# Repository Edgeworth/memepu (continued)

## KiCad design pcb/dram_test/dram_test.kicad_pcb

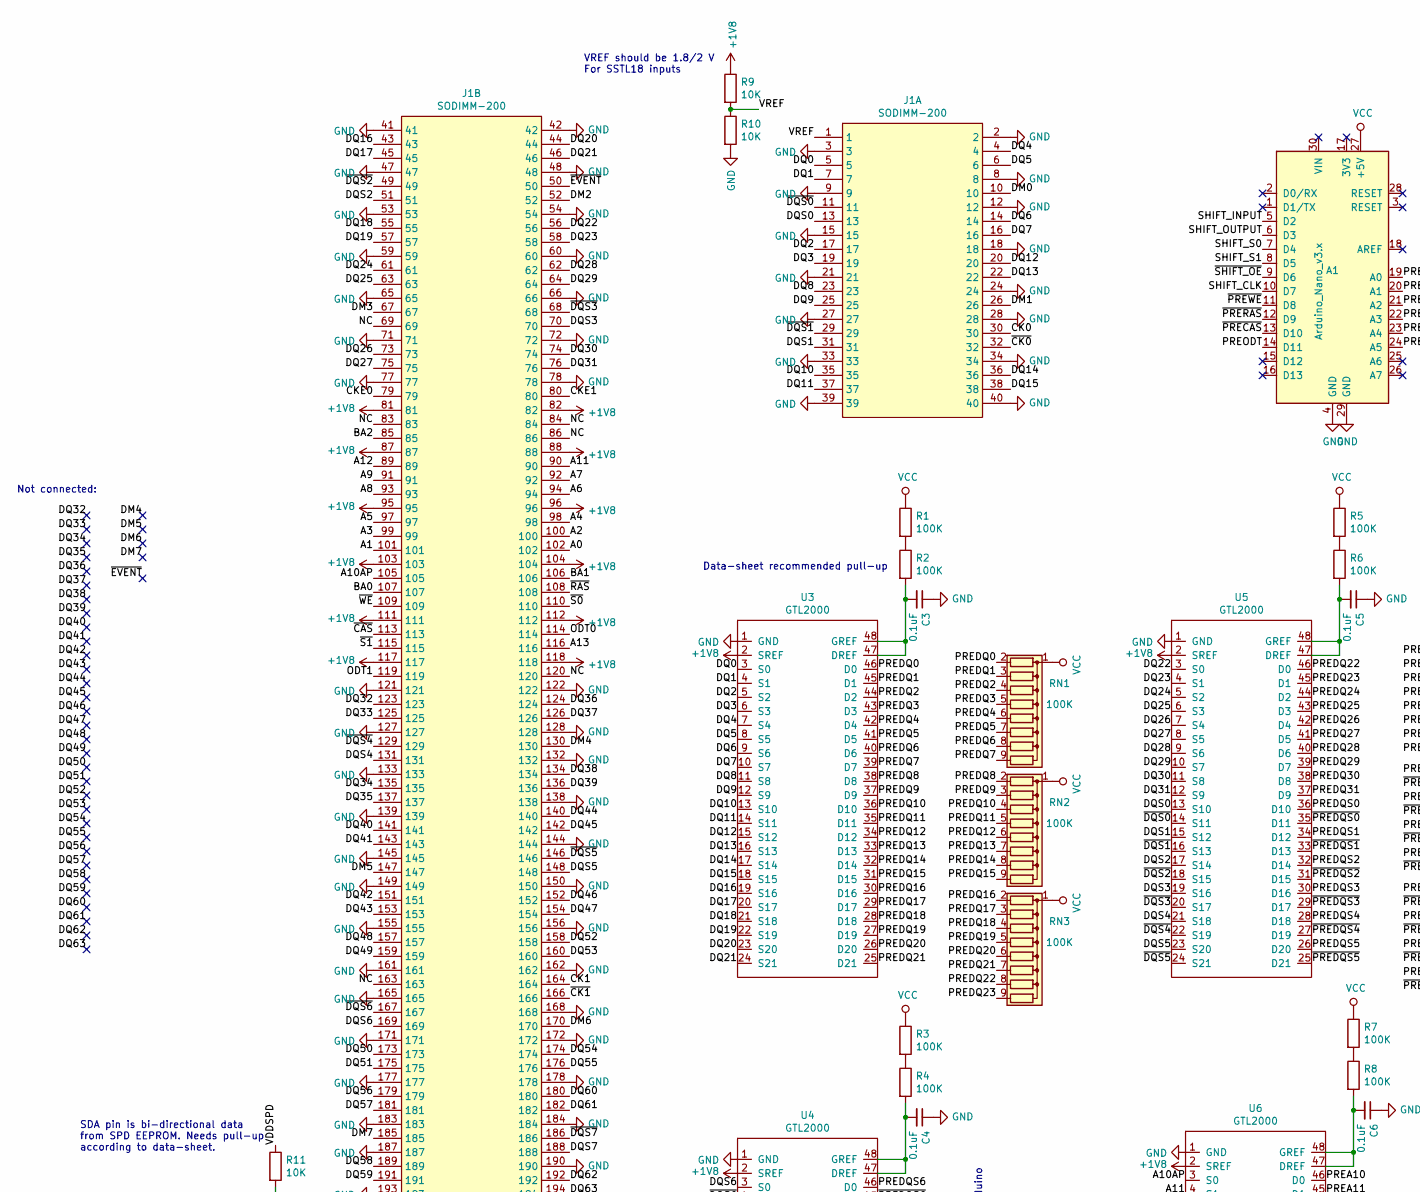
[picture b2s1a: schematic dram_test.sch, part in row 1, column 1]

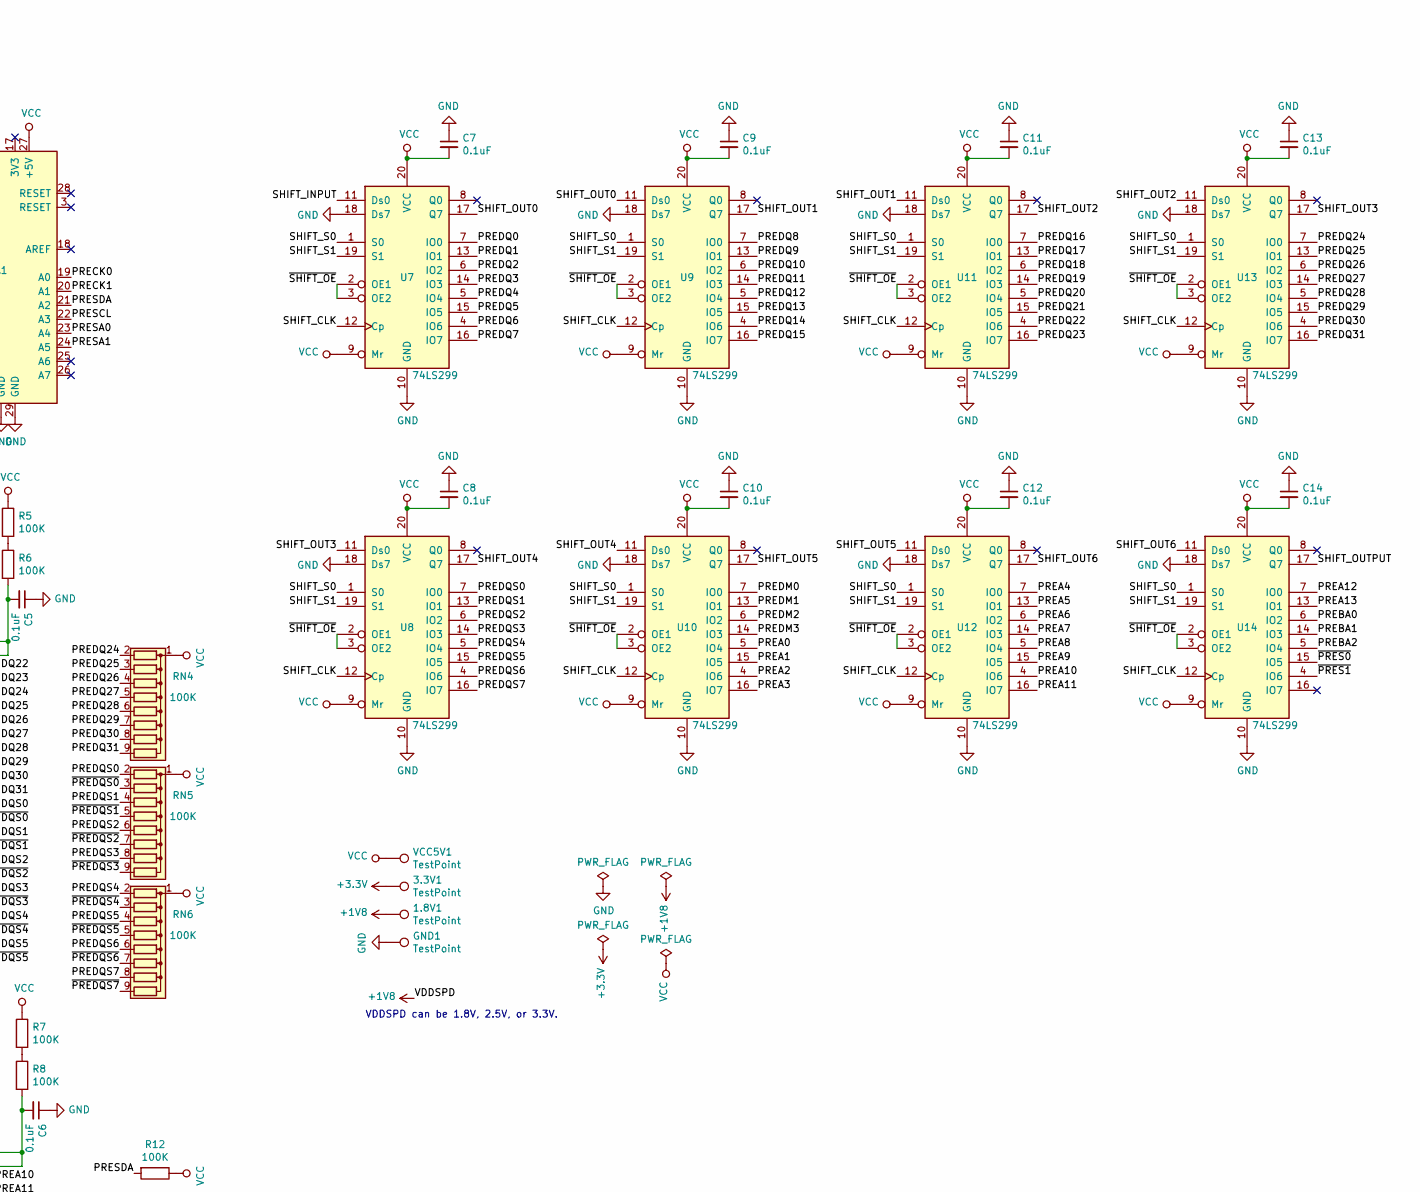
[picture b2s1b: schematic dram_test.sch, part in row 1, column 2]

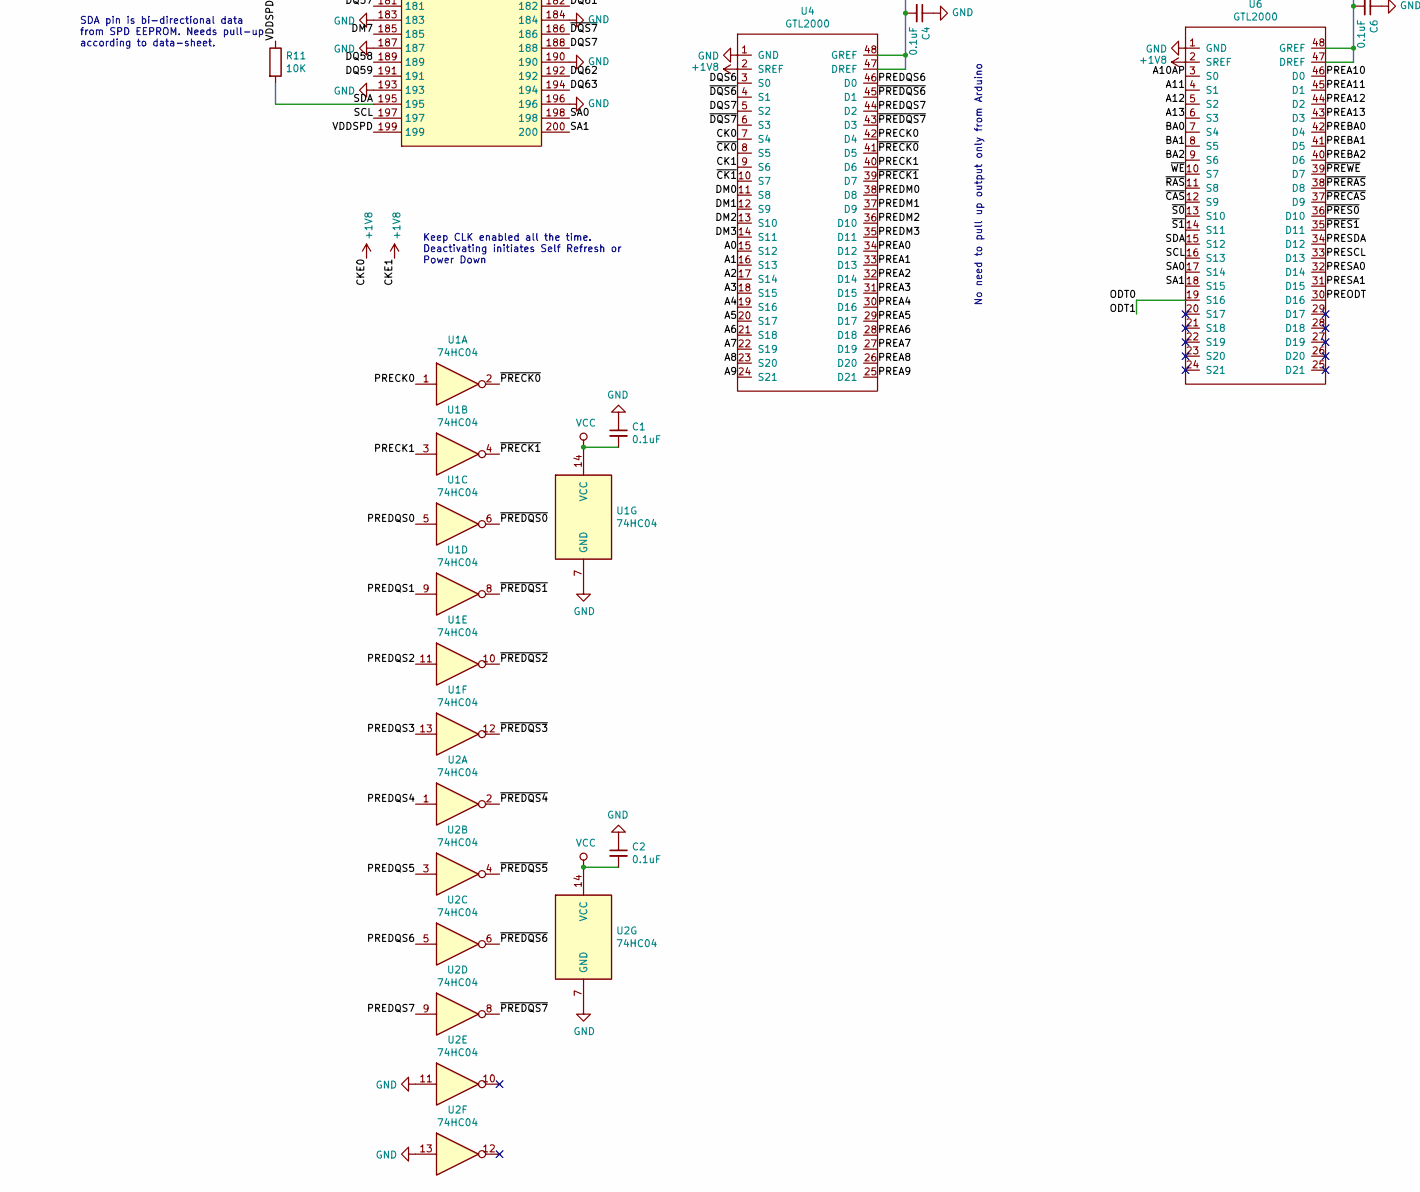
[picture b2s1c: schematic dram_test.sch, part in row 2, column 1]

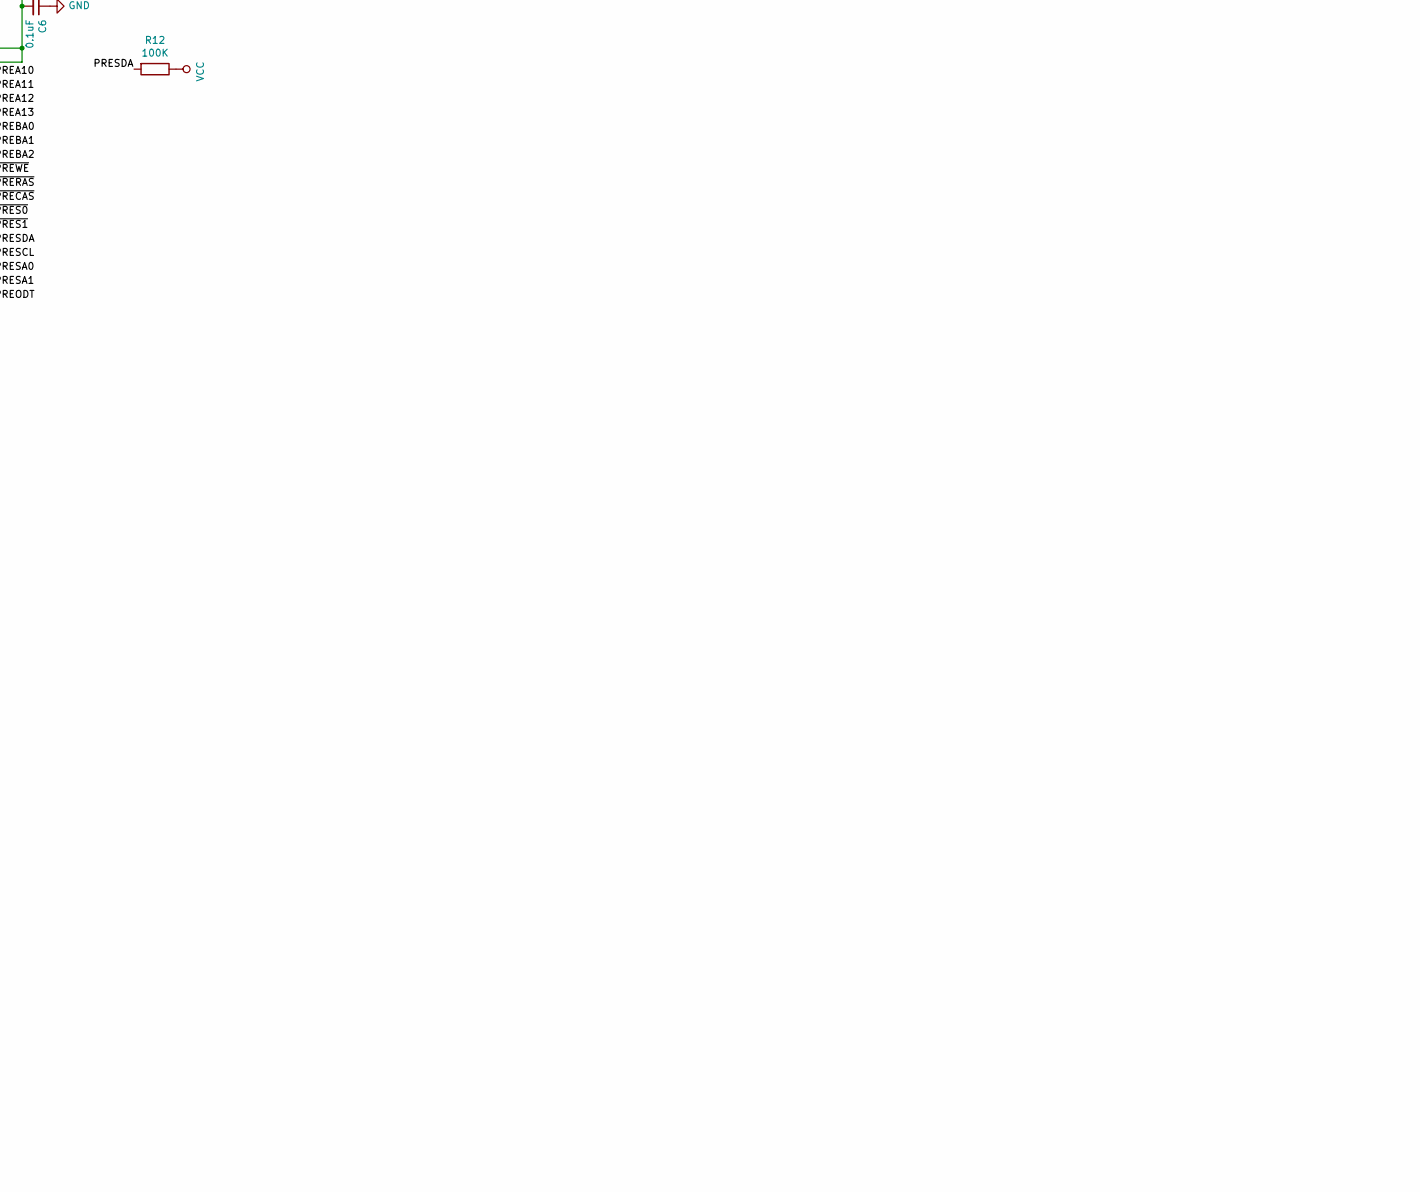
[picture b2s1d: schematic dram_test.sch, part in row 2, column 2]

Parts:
1.8V1, 3.3V1: TestPoint; TestPoint_Bridge_Pitch5.08mm_Drill1.3mm
A1: Arduino_Nano_v3.x; Arduino_Nano
C1, C2, C3, C4, C5, C6, C7, C8, C9, C10, C11, C12, C13, C14: 0.1uF; C_Disc_D6.0mm_W2.5mm_P5.00mm
GND1: TestPoint; TestPoint_Bridge_Pitch5.08mm_Drill1.3mm
J1: SODIMM-200; Socket_SODIMM_DDR1-2_TE_1612618
R1, R2, R3, R4, R5, R6, R7, R8, R12: 100K; R_Axial_DIN0207_L6.3mm_D2.5mm_P10.16mm_Horizontal
R9, R10, R11: 10K; R_Axial_DIN0207_L6.3mm_D2.5mm_P10.16mm_Horizontal
RN1, RN2, RN3, RN4, RN5, RN6: 100K; R_Array_SIP9
U1, U2: 74HC04; DIP-14_W7.62mm_Socket
U3, U4, U5, U6: GTL2000; TSSOP-48_6.1x12.5mm_P0.5mm
U7, U8, U9, U10, U11, U12, U13, U14: 74LS299; DIP-20_W7.62mm_Socket
VCC5V1: TestPoint; TestPoint_Bridge_Pitch5.08mm_Drill1.3mm

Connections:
+3V3: 3.3V1.1
/A0: J1.102, U4.15 (S12)
/A1: J1.101, U4.16 (S13)
/A2: J1.100, U4.17 (S14)
/A3: J1.99, U4.18 (S15)
/A4: J1.98, U4.19 (S16)
/A5: J1.97, U4.20 (S17)
/A6: J1.94, U4.21 (S18)
/A7: J1.92, U4.22 (S19)
/A8: J1.93, U4.23 (S20)
/A9: J1.91, U4.24 (S21)
/A10AP: J1.105, U6.3 (S0)
/A11: J1.90, U6.4 (S1)
/A12: J1.89, U6.5 (S2)
/A13: J1.116, U6.6 (S3)
/BA0: J1.107, U6.7 (S4)
/BA1: J1.106, U6.8 (S5)
/BA2: J1.85, U6.9 (S6)
/CK0: J1.30, U4.7 (S4)
/CK1: J1.164, U4.9 (S6)
/DM0: J1.10, U4.11 (S8)
/DM1: J1.26, U4.12 (S9)
/DM2: J1.52, U4.13 (S10)
/DM3: J1.67, U4.14 (S11)
/DM4: J1.130
/DM5: J1.147
/DM6: J1.170
/DM7: J1.185
/DQ0: J1.5, U3.3 (S0)
/DQ1: J1.7, U3.4 (S1)
/DQ2: J1.17, U3.5 (S2)
/DQ3: J1.19, U3.6 (S3)
/DQ4: J1.4, U3.7 (S4)
/DQ5: J1.6, U3.8 (S5)
/DQ6: J1.14, U3.9 (S6)
/DQ7: J1.16, U3.10 (S7)
/DQ8: J1.23, U3.11 (S8)
/DQ9: J1.25, U3.12 (S9)
/DQ10: J1.35, U3.13 (S10)
/DQ11: J1.37, U3.14 (S11)
/DQ12: J1.20, U3.15 (S12)
/DQ13: J1.22, U3.16 (S13)
/DQ14: J1.36, U3.17 (S14)
/DQ15: J1.38, U3.18 (S15)
/DQ16: J1.43, U3.19 (S16)
/DQ17: J1.45, U3.20 (S17)
/DQ18: J1.55, U3.21 (S18)
/DQ19: J1.57, U3.22 (S19)
/DQ20: J1.44, U3.23 (S20)
/DQ21: J1.46, U3.24 (S21)
/DQ22: J1.56, U5.3 (S0)
/DQ23: J1.58, U5.4 (S1)
/DQ24: J1.61, U5.5 (S2)
/DQ25: J1.63, U5.6 (S3)
/DQ26: J1.73, U5.7 (S4)
/DQ27: J1.75, U5.8 (S5)
/DQ28: J1.62, U5.9 (S6)
/DQ29: J1.64, U5.10 (S7)
/DQ30: J1.74, U5.11 (S8)
/DQ31: J1.76, U5.12 (S9)
/DQ32: J1.123
/DQ33: J1.125
/DQ34: J1.135
/DQ35: J1.137
/DQ36: J1.124
/DQ37: J1.126
/DQ38: J1.134
/DQ39: J1.136
/DQ40: J1.141
/DQ41: J1.143
/DQ42: J1.151
/DQ43: J1.153
/DQ44: J1.140
/DQ45: J1.142
/DQ46: J1.152
/DQ47: J1.154
/DQ48: J1.157
/DQ49: J1.159
/DQ50: J1.173
/DQ51: J1.175
/DQ52: J1.158
/DQ53: J1.160
/DQ54: J1.174
/DQ55: J1.176
/DQ56: J1.179
/DQ57: J1.181
/DQ58: J1.189
/DQ59: J1.191
/DQ60: J1.180
/DQ61: J1.182
/DQ62: J1.192
/DQ63: J1.194
/DQS0: J1.13, U5.13 (S10)
/DQS1: J1.31, U5.15 (S12)
/DQS2: J1.51, U5.17 (S14)
/DQS3: J1.70, U5.19 (S16)
/DQS4: J1.131, U5.21 (S18)
/DQS5: J1.148, U5.23 (S20)
/DQS6: J1.169, U4.3 (S0)
/DQS7: J1.188, U4.5 (S2)
/NC: J1.69, J1.83, J1.84, J1.86, J1.120, J1.163
/PREA0: U4.34 (D12), U10.5 (IO4)
/PREA1: U4.33 (D13), U10.15 (IO5)
/PREA2: U4.32 (D14), U10.4 (IO6)
/PREA3: U4.31 (D15), U10.16 (IO7)
/PREA4: U4.30 (D16), U12.7 (IO0)
/PREA5: U4.29 (D17), U12.13 (IO1)
/PREA6: U4.28 (D18), U12.6 (IO2)
/PREA7: U4.27 (D19), U12.14 (IO3)
/PREA8: U4.26 (D20), U12.5 (IO4)
/PREA9: U4.25 (D21), U12.15 (IO5)
/PREA10: U6.46 (D0), U12.4 (IO6)
/PREA11: U6.45 (D1), U12.16 (IO7)
/PREA12: U6.44 (D2), U14.7 (IO0)
/PREA13: U6.43 (D3), U14.13 (IO1)
/PREBA0: U6.42 (D4), U14.6 (IO2)
/PREBA1: U6.41 (D5), U14.14 (IO3)
/PREBA2: U6.40 (D6), U14.5 (IO4)
/PRECK0: A1.19 (A0), U1.1, U4.42 (D4)
/PRECK1: A1.20 (A1), U1.3, U4.40 (D6)
/PREDM0: U4.38 (D8), U10.7 (IO0)
/PREDM1: U4.37 (D9), U10.13 (IO1)
/PREDM2: U4.36 (D10), U10.6 (IO2)
/PREDM3: U4.35 (D11), U10.14 (IO3)
/PREDQ0: RN1.2 (R1), U3.46 (D0), U7.7 (IO0)
/PREDQ1: RN1.3 (R2), U3.45 (D1), U7.13 (IO1)
/PREDQ2: RN1.4 (R3), U3.44 (D2), U7.6 (IO2)
/PREDQ3: RN1.5 (R4), U3.43 (D3), U7.14 (IO3)
/PREDQ4: RN1.6 (R5), U3.42 (D4), U7.5 (IO4)
/PREDQ5: RN1.7 (R6), U3.41 (D5), U7.15 (IO5)
/PREDQ6: RN1.8 (R7), U3.40 (D6), U7.4 (IO6)
/PREDQ7: RN1.9 (R8), U3.39 (D7), U7.16 (IO7)
/PREDQ8: RN2.2 (R1), U3.38 (D8), U9.7 (IO0)
/PREDQ9: RN2.3 (R2), U3.37 (D9), U9.13 (IO1)
/PREDQ10: RN2.4 (R3), U3.36 (D10), U9.6 (IO2)
/PREDQ11: RN2.5 (R4), U3.35 (D11), U9.14 (IO3)
/PREDQ12: RN2.6 (R5), U3.34 (D12), U9.5 (IO4)
/PREDQ13: RN2.7 (R6), U3.33 (D13), U9.15 (IO5)
/PREDQ14: RN2.8 (R7), U3.32 (D14), U9.4 (IO6)
/PREDQ15: RN2.9 (R8), U3.31 (D15), U9.16 (IO7)
/PREDQ16: RN3.2 (R1), U3.30 (D16), U11.7 (IO0)
/PREDQ17: RN3.3 (R2), U3.29 (D17), U11.13 (IO1)
/PREDQ18: RN3.4 (R3), U3.28 (D18), U11.6 (IO2)
/PREDQ19: RN3.5 (R4), U3.27 (D19), U11.14 (IO3)
/PREDQ20: RN3.6 (R5), U3.26 (D20), U11.5 (IO4)
/PREDQ21: RN3.7 (R6), U3.25 (D21), U11.15 (IO5)
/PREDQ22: RN3.8 (R7), U5.46 (D0), U11.4 (IO6)
/PREDQ23: RN3.9 (R8), U5.45 (D1), U11.16 (IO7)
/PREDQ24: RN4.2 (R1), U5.44 (D2), U13.7 (IO0)
/PREDQ25: RN4.3 (R2), U5.43 (D3), U13.13 (IO1)
/PREDQ26: RN4.4 (R3), U5.42 (D4), U13.6 (IO2)
/PREDQ27: RN4.5 (R4), U5.41 (D5), U13.14 (IO3)
/PREDQ28: RN4.6 (R5), U5.40 (D6), U13.5 (IO4)
/PREDQ29: RN4.7 (R6), U5.39 (D7), U13.15 (IO5)
/PREDQ30: RN4.8 (R7), U5.38 (D8), U13.4 (IO6)
/PREDQ31: RN4.9 (R8), U5.37 (D9), U13.16 (IO7)
/PREDQS0: RN5.2 (R1), U1.5, U5.36 (D10), U8.7 (IO0)
/PREDQS1: RN5.4 (R3), U1.9, U5.34 (D12), U8.13 (IO1)
/PREDQS2: RN5.6 (R5), U1.11, U5.32 (D14), U8.6 (IO2)
/PREDQS3: RN5.8 (R7), U1.13, U5.30 (D16), U8.14 (IO3)
/PREDQS4: RN6.2 (R1), U2.1, U5.28 (D18), U8.5 (IO4)
/PREDQS5: RN6.4 (R3), U2.3, U5.26 (D20), U8.15 (IO5)
/PREDQS6: RN6.6 (R5), U2.5, U4.46 (D0), U8.4 (IO6)
/PREDQS7: RN6.8 (R7), U2.9, U4.44 (D2), U8.16 (IO7)
/PREODT: A1.14 (D11), U6.30 (D16)
/PRESA0: A1.23 (A4), U6.32 (D14)
/PRESA1: A1.24 (A5), U6.31 (D15)
/PRESCL: A1.22 (A3), U6.33 (D13)
/PRESDA: A1.21 (A2), R12.2, U6.34 (D12)
/SA0: J1.198, U6.17 (S14)
/SA1: J1.200, U6.18 (S15)
/SCL: J1.197, U6.16 (S13)
/SDA: J1.195, R11.2, U6.15 (S12)
/SHIFT_CLK: A1.10 (D7), U7.12 (Cp), U8.12 (Cp), U9.12 (Cp), U10.12 (Cp), U11.12 (Cp), U12.12 (Cp), U13.12 (Cp), U14.12 (Cp)
/SHIFT_INPUT: A1.5 (D2), U7.11 (Ds0)
/SHIFT_OUT0: U7.17 (Q7), U9.11 (Ds0)
/SHIFT_OUT1: U9.17 (Q7), U11.11 (Ds0)
/SHIFT_OUT2: U11.17 (Q7), U13.11 (Ds0)
/SHIFT_OUT3: U8.11 (Ds0), U13.17 (Q7)
/SHIFT_OUT4: U8.17 (Q7), U10.11 (Ds0)
/SHIFT_OUT5: U10.17 (Q7), U12.11 (Ds0)
/SHIFT_OUT6: U12.17 (Q7), U14.11 (Ds0)
/SHIFT_OUTPUT: A1.6 (D3), U14.17 (Q7)
/SHIFT_S0: A1.7 (D4), U7.1 (S0), U8.1 (S0), U9.1 (S0), U10.1 (S0), U11.1 (S0), U12.1 (S0), U13.1 (S0), U14.1 (S0)
/SHIFT_S1: A1.8 (D5), U7.19 (S1), U8.19 (S1), U9.19 (S1), U10.19 (S1), U11.19 (S1), U12.19 (S1), U13.19 (S1), U14.19 (S1)
/VREF: J1.1, R9.2, R10.1
/~CAS: J1.113, U6.12 (S9)
/~CK0: J1.32, U4.8 (S5)
/~CK1: J1.166, U4.10 (S7)
/~DQS0: J1.11, U5.14 (S11)
/~DQS1: J1.29, U5.16 (S13)
/~DQS2: J1.49, U5.18 (S15)
/~DQS3: J1.68, U5.20 (S17)
/~DQS4: J1.129, U5.22 (S19)
/~DQS5: J1.146, U5.24 (S21)
/~DQS6: J1.167, U4.4 (S1)
/~DQS7: J1.186, U4.6 (S3)
/~EVENT: J1.50
/~PRECAS: A1.13 (D10), U6.37 (D9)
/~PRECK0: U1.2, U4.41 (D5)
/~PRECK1: U1.4, U4.39 (D7)
/~PREDQS0: RN5.3 (R2), U1.6, U5.35 (D11)
/~PREDQS1: RN5.5 (R4), U1.8, U5.33 (D13)
/~PREDQS2: RN5.7 (R6), U1.10, U5.31 (D15)
/~PREDQS3: RN5.9 (R8), U1.12, U5.29 (D17)
/~PREDQS4: RN6.3 (R2), U2.2, U5.27 (D19)
/~PREDQS5: RN6.5 (R4), U2.4, U5.25 (D21)
/~PREDQS6: RN6.7 (R6), U2.6, U4.45 (D1)
/~PREDQS7: RN6.9 (R8), U2.8, U4.43 (D3)
/~PRERAS: A1.12 (D9), U6.38 (D8)
/~PRES0: U6.36 (D10), U14.15 (IO5)
/~PRES1: U6.35 (D11), U14.4 (IO6)
/~PREWE: A1.11 (D8), U6.39 (D7)
/~RAS: J1.108, U6.11 (S8)
/~S0: J1.110, U6.13 (S10)
/~S1: J1.115, U6.14 (S11)
/~SHIFT_OE: A1.9 (D6), U7.2 (OE1), U7.3 (OE2), U8.2 (OE1), U8.3 (OE2), U9.2 (OE1), U9.3 (OE2), U10.2 (OE1), U10.3 (OE2), U11.2 (OE1), U11.3 (OE2), U12.2 (OE1), U12.3 (OE2), U13.2 (OE1), U13.3 (OE2), U14.2 (OE1), U14.3 (OE2)
/~WE: J1.109, U6.10 (S7)
GND: A1.4 (GND), A1.29 (GND), C1.1, C2.1, C3.1, C4.1, C5.1, C6.1, C7.1, C8.1, C9.1, C10.1, C11.1, C12.1, C13.1, C14.1, GND1.1, J1.2, J1.3, J1.8, J1.9, J1.12, J1.15, J1.18, J1.21, J1.24, J1.27, J1.28, J1.33, J1.34, J1.39, J1.40, J1.41, J1.42, J1.47, J1.48, J1.53, J1.54, J1.59, J1.60, J1.65, J1.66, J1.71, J1.72, J1.77, J1.78, J1.121, J1.122, J1.127, J1.128, J1.132, J1.133, J1.138, J1.139, J1.144, J1.145, J1.149, J1.150, J1.155, J1.156, J1.161, J1.162, J1.165, J1.168, J1.171, J1.172, J1.177, J1.178, J1.183, J1.184, J1.187, J1.190, J1.193, J1.196, R10.2, U1.7 (GND), U2.7 (GND), U2.11, U2.13, U3.1 (GND), U4.1 (GND), U5.1 (GND), U6.1 (GND), U7.10 (GND), U7.18 (Ds7), U8.10 (GND), U8.18 (Ds7), U9.10 (GND), U9.18 (Ds7), U10.10 (GND), U10.18 (Ds7), U11.10 (GND), U11.18 (Ds7), U12.10 (GND), U12.18 (Ds7), U13.10 (GND), U13.18 (Ds7), U14.10 (GND), U14.18 (Ds7)
unnamed: C3.2, R2.2, U3.47 (DREF), U3.48 (GREF)
unnamed: C4.2, R4.2, U4.47 (DREF), U4.48 (GREF)
unnamed: C5.2, R6.2, U5.47 (DREF), U5.48 (GREF)
unnamed: C6.2, R8.2, U6.47 (DREF), U6.48 (GREF)
unnamed: R1.2, R2.1
unnamed: R3.2, R4.1
unnamed: R5.2, R6.1
unnamed: R7.2, R8.1
VCC: A1.27 (+5V), C1.2, C2.2, C7.2, C8.2, C9.2, C10.2, C11.2, C12.2, C13.2, C14.2, R1.1, R3.1, R5.1, R7.1, R12.1, RN1.1 (common), RN2.1 (common), RN3.1 (common), RN4.1 (common), RN5.1 (common), RN6.1 (common), U1.14 (VCC), U2.14 (VCC), U7.9 (Mr), U7.20 (VCC), U8.9 (Mr), U8.20 (VCC), U9.9 (Mr), U9.20 (VCC), U10.9 (Mr), U10.20 (VCC), U11.9 (Mr), U11.20 (VCC), U12.9 (Mr), U12.20 (VCC), U13.9 (Mr), U13.20 (VCC), U14.9 (Mr), U14.20 (VCC), VCC5V1.1

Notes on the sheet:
No need to pull up output only from Arduino
Not connected:
Keep CLK enabled all the time. Deactivating initiates Self Refresh or Power Down
Data-sheet recommended pull-up
SDA pin is bi-directional data from SPD EEPROM. Needs pull-up according to data-sheet.
VDDSPD can be 1.8V, 2.5V, or 3.3V.
VREF should be 1.8/2 V For SSTL18 inputs

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
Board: 2 copper layers, 52 parts (10 on the bottom side), 193 nets, no tracks yet.
